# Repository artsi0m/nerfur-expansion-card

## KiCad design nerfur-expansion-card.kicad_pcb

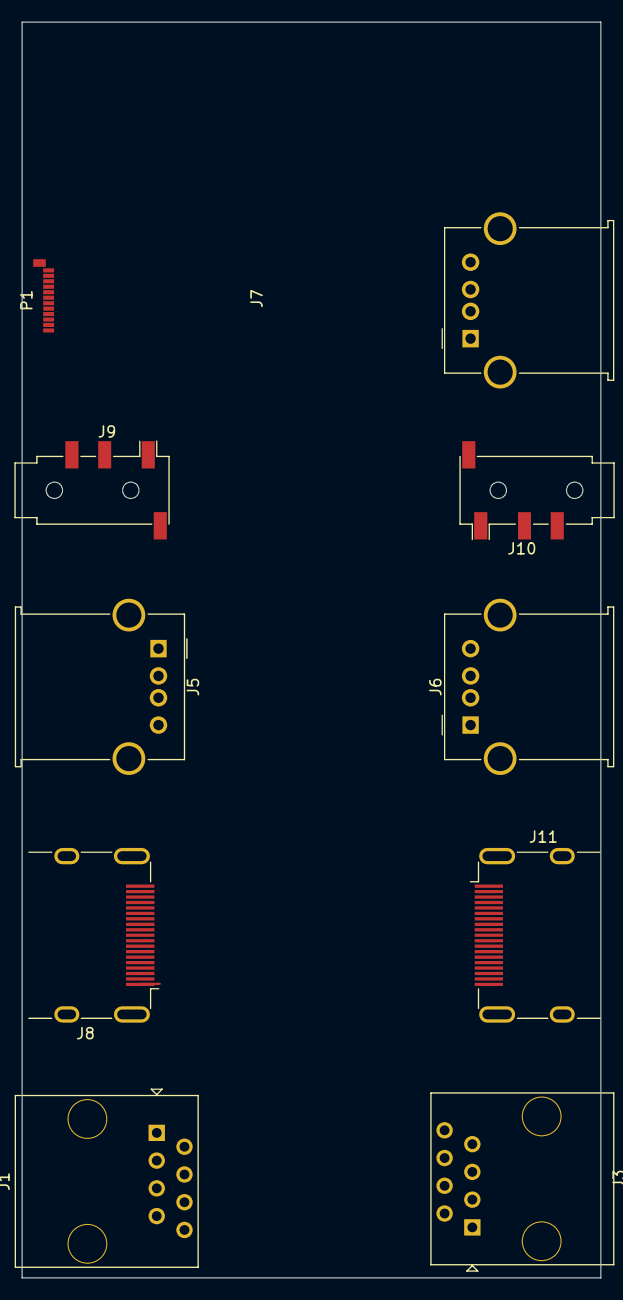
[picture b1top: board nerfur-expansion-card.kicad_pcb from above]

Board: 4 copper layers, 53.0 x 115.0 mm, 10 parts (0 on the bottom side), 42 nets.

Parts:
J1, J3: RJ45; RJ45_OST_PJ012-8P8CX_Vertical
J5, J6, J7: USB_A; USB_A_Molex_67643_Horizontal
J8, J11: HDMI_A; HDMI_A_Molex_208658-1001_Horizontal
J9, J10: AudioJack4; Jack_3.5mm_PJ320D_Horizontal
P1: USB_C_Plug; USB_C_Plug_Molex_105444

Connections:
/HDMI-CK+: J8.10 (CK+), J11.10 (CK+)
/HDMI-CK-: J8.12 (CK-), J11.12 (CK-)
/HDMI-D0+: J8.7 (D0+), J11.7 (D0+)
/HDMI-D0-: J8.9 (D0-), J11.9 (D0-)
/HDMI-D1+: J8.4 (D1+), J11.4 (D1+)
/HDMI-D1-: J8.6 (D1-), J11.6 (D1-)
/HDMI-D2+: J8.1 (D2+), J11.1 (D2+)
/HDMI-D2-: J8.3 (D2-), J11.3 (D2-)
/USB-A-USB-A-D+: J5.3 (D+), J6.3 (D+)
/USB-A-USB-A-D-: J5.2 (D-), J6.2 (D-)
/USB-C-USB-A-D+: J7.3 (D+), P1.A6 (D+)
/USB-C-USB-A-D-: J7.2 (D-), P1.A7 (D-)
unnamed: J1.1, J3.1
unnamed: J1.2, J3.2
unnamed: J1.3, J3.3
unnamed: J1.4, J3.4
unnamed: J1.5, J3.5
unnamed: J1.6, J3.6
unnamed: J1.7, J3.7
unnamed: J1.8, J3.8
unnamed: J5.4 (GND), J6.4 (GND)
unnamed: J5.5 (Shield), J6.5 (Shield)
unnamed: J5.1 (VBUS), J6.1 (VBUS)
unnamed: J7.4 (GND), P1.A1 (GND), P1.A12 (GND), P1.B1 (GND), P1.B12 (GND)
unnamed: J7.5 (Shield), P1.S1 (SHIELD)
unnamed: J7.1 (VBUS), P1.A4 (VBUS), P1.A9 (VBUS), P1.B4 (VBUS), P1.B9 (VBUS)
unnamed: J9.R1, J10.R1
unnamed: J9.R2, J10.R2
unnamed: J9.S, J10.S
unnamed: J9.T, J10.T
unnamed: J8.18 (+5V), J11.18 (+5V)
unnamed: J8.13 (CEC), J11.13 (CEC)
unnamed: J8.11 (CKS), J11.11 (CKS)
unnamed: J8.8 (D0S), J11.8 (D0S)
unnamed: J8.5 (D1S), J11.5 (D1S)
unnamed: J8.2 (D2S), J11.2 (D2S)
unnamed: J8.17 (GND), J11.17 (GND)
unnamed: J8.19 (HPD), J11.19 (HPD)
unnamed: J8.SH, J11.SH
unnamed: J8.15 (SCL), J11.15 (SCL)
unnamed: J8.16 (SDA), J11.16 (SDA)
unnamed: J8.14 (UTILITY), J11.14 (UTILITY)

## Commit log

2025-01-21 gitignore for KiCAD
2025-01-21 initial commit for schematic
2025-01-21 Assigned footprints
2025-01-21 differential pairs
2025-07-08 kicad-v9 s-expressions
2025-07-08 project file and pcb file
2025-09-05 schematics: TVS diode arrays on HDMI grounding
2025-09-13 add tech
2025-09-19 Markdown file extension
2025-09-19 Переформатировал техническое задание немного.
2025-09-19 Упростил таблицу из ТЗ
